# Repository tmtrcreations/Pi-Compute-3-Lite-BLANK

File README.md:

# Pi-Compute-3-Lite-BLANK
******************************************
PROJECT HAS BEEN UPDATED TO KICAD V5.0!
******************************************

The schematic will require some custom parts that can be found in our other repository [RPi_CM3_Parts](https://github.com/tmtrcreations/RPi_CM3_Parts). The schematic contains everything required to get the CM3L to run. The rest of the pins are free to be used for any project. These files are meant to help jumpstart a project that wants to build around the CM3L.

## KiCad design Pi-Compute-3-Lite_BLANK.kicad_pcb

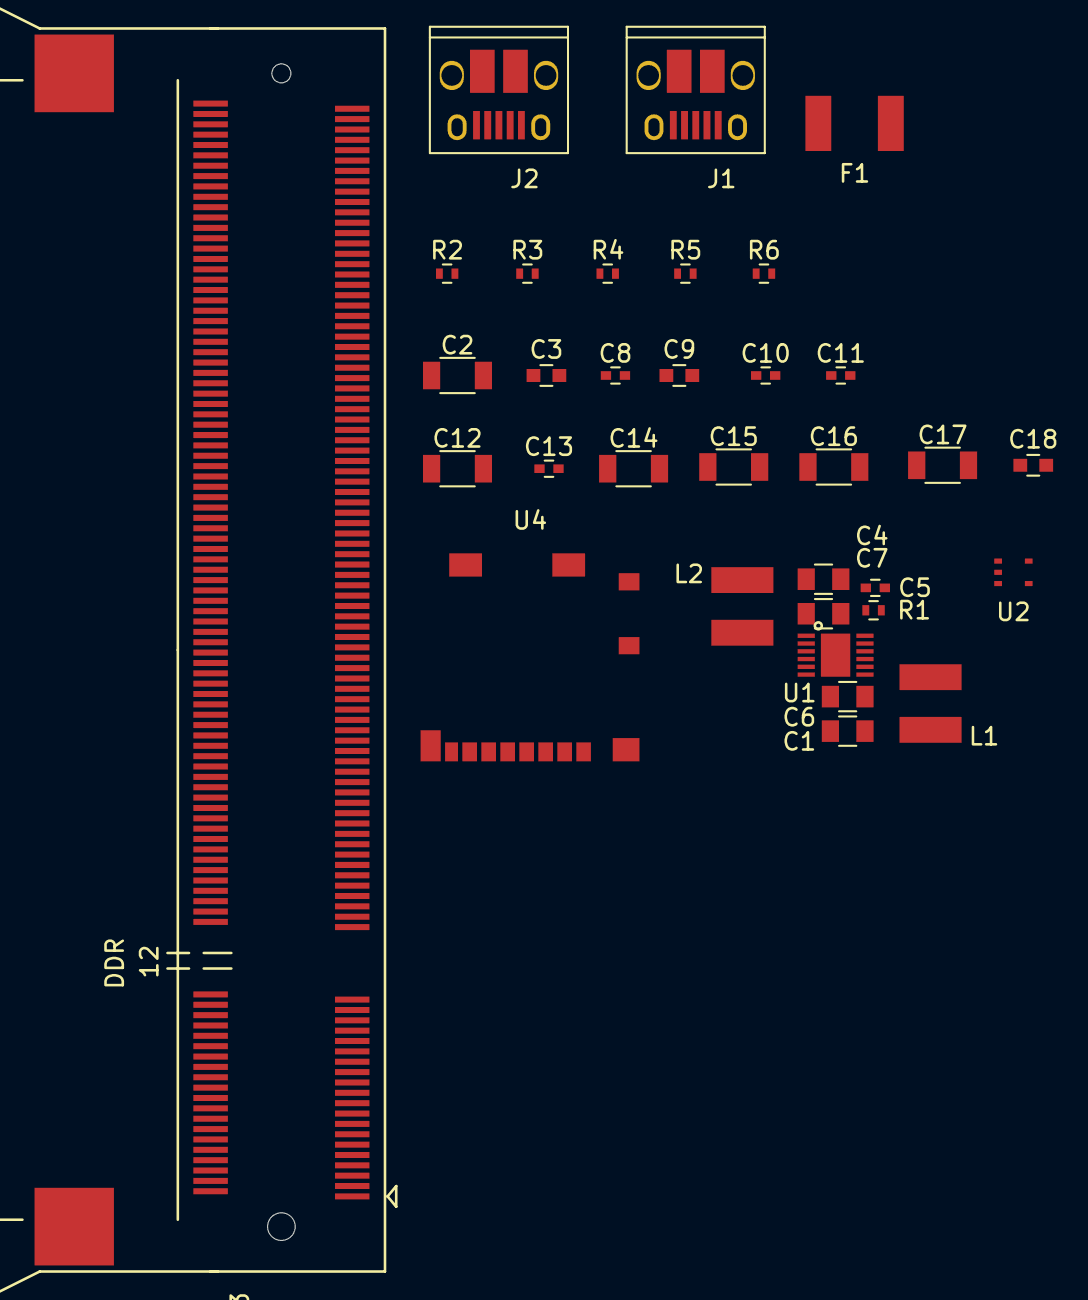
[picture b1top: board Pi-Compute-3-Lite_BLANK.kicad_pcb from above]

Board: 2 copper layers, 33 parts (0 on the bottom side), 23 nets, no tracks yet.

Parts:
C1, C4, C6, C7: 10uF; C_0805
C2, C12, C14, C15, C16, C17: 47uF; C_1206
C3, C9, C18: 4.7uF; C_0603
C5, C10: 100nF; C_0402
C8, C11, C13: 1uF; C_0402
F1: MF-MSMF200
J1, J2: USB_OTG; USB_Micro-B_10103594-0001LF
L1, L2: 4.7uH; SRN4018-4R7M
R1, R2, R3, R4, R5, R6: 100k; R_0402
U1: PAM2306AYPKE
U2: AP7115-25SEG; AP7115-25SEG-7
U3: DDR2_SODIMM_CM_3_Lite; Socket_SODIMM_DDR2
U4: 1040310811; uSD_1040310811

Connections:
1V8: C4.1, C15.1, L2.2, U1.10, U3.183, U3.184, U3.185, U3.186
3V3: C1.1, C3.1, C8.1, C11.1, C13.1, C14.1, C18.1, L1.2, U1.4, U2.1, U2.3, U3.2, U3.4, U3.6, U3.39, U3.40, U3.41, U3.42, U3.191, U3.192, U3.193, U3.194, U4.4
5V: C2.1, C6.1, C7.1, C12.1, C16.1, C17.1, F1.2, J2.1, R1.1, U1.1, U1.6, U1.7, U3.197, U3.198, U3.199, U3.200
CM_VDAC: C9.1, U2.5, U3.189, U3.190
GND: C1.2, C2.2, C3.2, C4.2, C5.2, C6.2, C7.2, C8.2, C9.2, C10.2, C11.2, C12.2, C13.2, C14.2, C15.2, C16.2, C17.2, C18.2, J1.5, J1.6, J2.5, J2.6, R2.2, R3.2, R4.2, R5.2, R6.2, U1.3, U1.9, U1.13, U2.2, U3.1, U3.7, U3.8, U3.13, U3.14, U3.19, U3.20, U3.25, U3.26, U3.31, U3.32, U3.37, U3.38, U3.43, U3.44, U3.49, U3.50, U3.55, U3.56, U3.61, U3.62, U3.67, U3.68, U3.73, U3.74, U3.79, U3.80, U3.85, U3.86, U3.91, U3.92, U3.97, U3.98, U3.103, U3.104, U3.109, U3.110, U3.115, U3.116, U3.121, U3.122, U3.127, U3.133, U3.134, U3.139, U3.140, U3.145, U3.146, U3.151, U3.152, U3.157, U3.163, U3.164, U3.169, U3.170, U3.181, U3.182, U3.187, U3.188, U3.195, U3.196, U4.6, U4.11, U4.12, U4.13, U4.14
unnamed: C5.1, R1.2, U1.12
unnamed: C10.1, U2.4
unnamed: F1.1, J1.1
unnamed: L1.1, U1.8
unnamed: L2.1, U1.2
unnamed: R2.1, U3.30
unnamed: R3.1, U3.28
unnamed: R4.1, U3.84
unnamed: R5.1, U3.82
unnamed: R6.1, U3.88
SDX_CLK: U3.10, U4.5
SDX_CMD: U3.12, U4.3
SDX_D0: U3.16, U4.7
SDX_D1: U3.18, U4.8
SDX_D2: U3.22, U4.1
SDX_D3: U3.24, U4.2
USB_D+: J2.3, U3.165
USB_D-: J2.2, U3.167

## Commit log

2017-07-23 Create LICENSE
2017-09-30 Bug fix
    Removed the dependence on an old library.
2017-09-30 Bug fix
2017-09-30 Continued bug fix
2017-09-30 Added footprints
    Added all of the custom footprints needed.
2017-09-30 Updated README.md
    Addresses known issues across various different versions of KiCad.
2017-10-01 Updated README.md
    Added note for versioning issues.
2017-10-01 Bug fix.
2017-10-01 Footprint assignment
2017-10-01 Fixed incorrect footprint
2017-10-01 Added SODIMM footprint
2018-09-01 Netlist and PCB added
2018-09-02 Added suggested power supply layout to PCB
2018-09-09 Fixed error
